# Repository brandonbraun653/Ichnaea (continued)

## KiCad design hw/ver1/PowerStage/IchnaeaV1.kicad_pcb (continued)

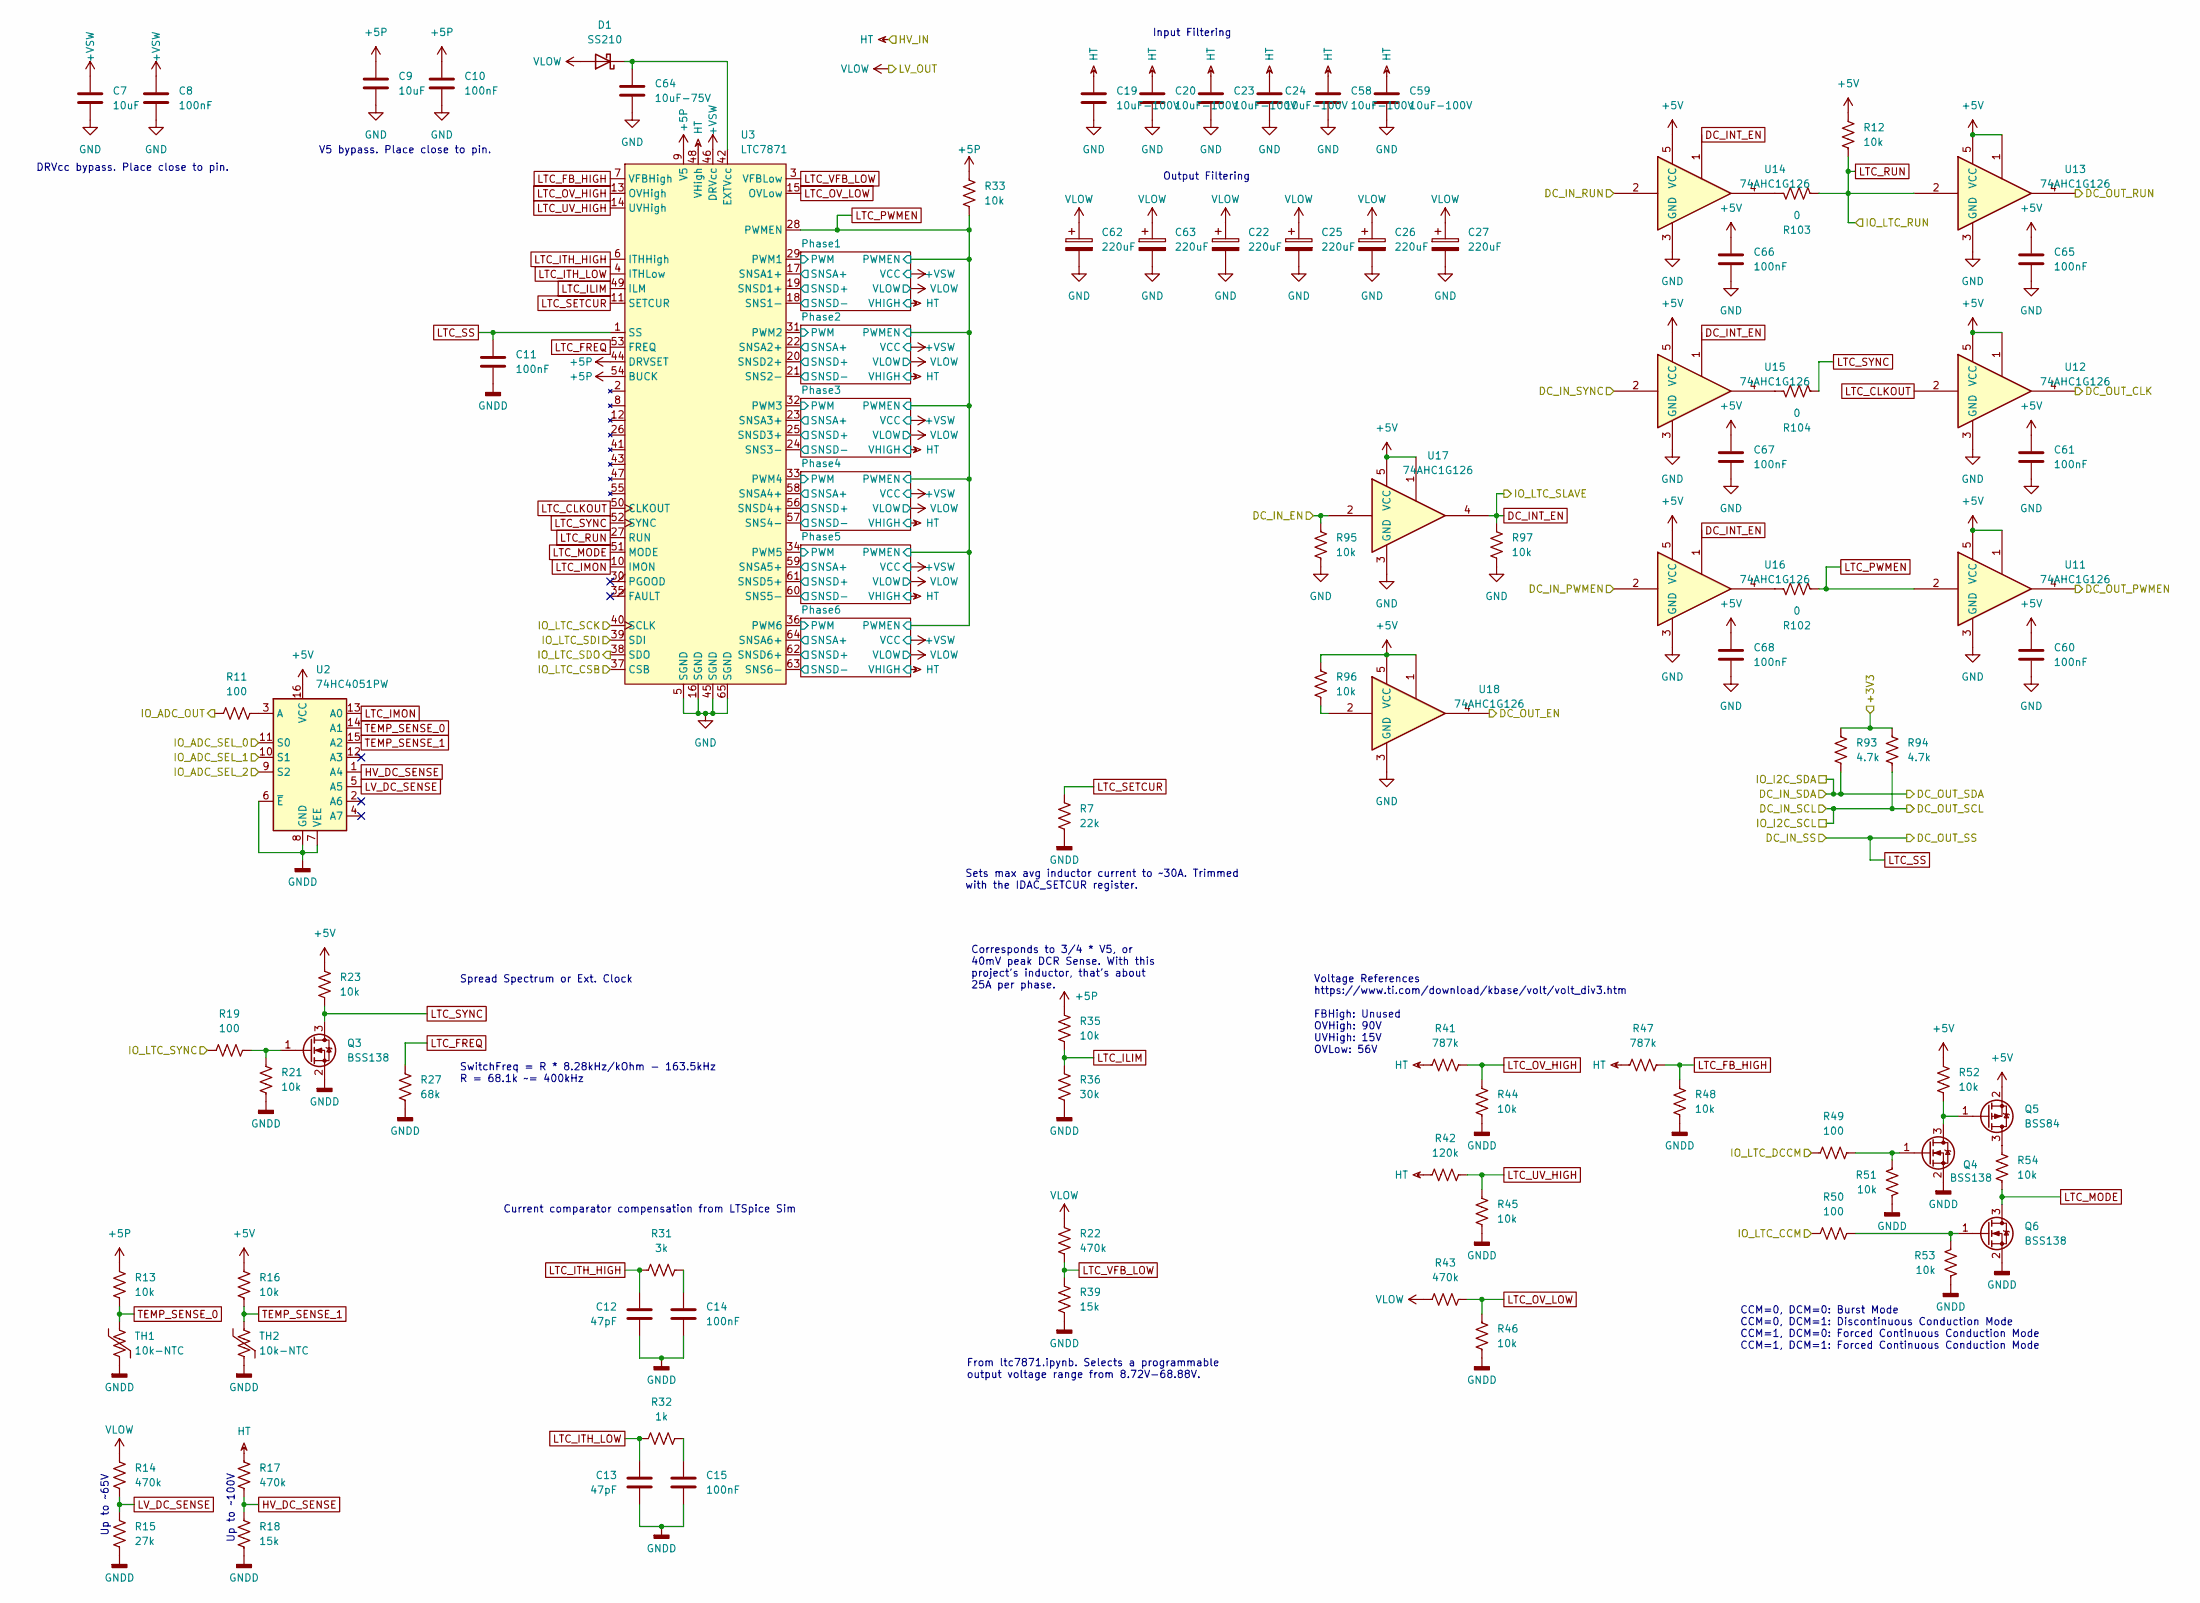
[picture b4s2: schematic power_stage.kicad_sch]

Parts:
C7, C9: 10uF; C_0603_1608Metric; Digikey N/A
C8, C10, C11, C14, C15, C60, C61, C65, C66, C67, C68: 100nF; C_0603_1608Metric; LCSC C14663
C12, C13: 47pF; C_0603_1608Metric; LCSC C1671
C19, C20, C23, C24, C58, C59: 10uF-100V; C_1210_3225Metric_Pad1.33x2.70mm_HandSolder; Digikey 490-16266-1-ND
C22, C25, C26, C27, C62, C63: 220uF; CP_Radial_D10.0mm_P5.00mm; Digikey 1189-3789-1-ND
C64: 10uF-75V; C_1210_3225Metric_Pad1.33x2.70mm_HandSolder; Digikey 445-CGA6P1X7R1N106M250ACCT-ND
D1: SS210; D_SMA; LCSC C14996
Q3, Q4, Q6: BSS138; SOT-23; Digikey 5272-BSS138CT-ND
Q5: BSS84; SOT-23; Digikey 5272-BSS84CT-ND
R7: 22k; R_0603_1608Metric; LCSC C31850
R11, R19, R49, R50: 100; R_0603_1608Metric; Digikey N/A
R12, R13, R16, R21, R23, R33, R35, R44, R45, R46, R48, R51, R52, R53, R54, R95, R96, R97: 10k; R_0603_1608Metric; LCSC C25804
R14: 470k; R_0603_1608Metric; Digikey N/A
R15: 27k; R_0603_1608Metric; Digikey N/A
R17, R22, R43: 470k; R_0603_1608Metric; LCSC C23178
R18: 15k; R_0603_1608Metric; Digikey N/A
R27: 68k; R_0603_1608Metric; Digikey N/A
R31: 3k; R_0603_1608Metric; Digikey N/A
R32: 1k; R_0603_1608Metric; Digikey N/A
R36: 30k; R_0603_1608Metric; Digikey N/A
R39: 15k; R_0603_1608Metric; LCSC C22809
R41, R47: 787k; R_0603_1608Metric_Pad0.98x0.95mm_HandSolder; Digikey P787KHCT-ND
R42: 120k; R_0603_1608Metric; Digikey N/A
R93, R94: 4.7k; R_0603_1608Metric; LCSC C23162
R102, R103, R104: 0; R_0603_1608Metric; Digikey N/A
TH1, TH2: 10k-NTC; R_0402_1005Metric_Pad0.72x0.64mm_HandSolder; Digikey 445-2550-1-ND
U2: 74HC4051PW; TSSOP-16_4.4x5mm_P0.65mm; Digikey 1727-3064-1-ND
U3: LTC7871; LQFP-64-1EP_10x10mm_P0.5mm_EP6.5x6.5mm; Digikey 505-LTC7871ELWE#PBF-ND
U11, U12, U13, U14, U15, U16, U17, U18: 74AHC1G126; SOT-353_SC-70-5_Handsoldering; Digikey 74AHCT1G126SE-7DICT-ND

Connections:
+3.3V: R93.2, R94.2; also elsewhere on the board
+5P: C9.1, C10.1, R13.2, R33.2, R35.2, U3.9 (V5), U3.44 (DRVSET), U3.54 (BUCK)
+5V: C60.1, C61.1, C65.1, C66.1, C67.1, C68.1, Q5.2 (S), R12.2, R16.2, R23.2, R52.2, R96.2, U2.16 (VCC), U11.1, U11.5 (VCC), U12.1, U12.5 (VCC), U13.1, U13.5 (VCC), U14.5 (VCC), U15.5 (VCC), U16.5 (VCC), U17.1, U17.5 (VCC), U18.1, U18.5 (VCC); also elsewhere on the board
+VSW: C7.1, C8.1, U3.46 (DRVcc); also elsewhere on the board
/ControlStage/CTL_IN_ADC: R11.1; also elsewhere on the board
/ControlStage/CTL_IN_SDI: U3.38 (SDO); also elsewhere on the board
/ControlStage/CTL_IO_SDA: R93.1; also elsewhere on the board
/ControlStage/CTL_OUT_ADC_SEL_0: U2.11 (S0); also elsewhere on the board
/ControlStage/CTL_OUT_ADC_SEL_1: U2.10 (S1); also elsewhere on the board
/ControlStage/CTL_OUT_ADC_SEL_2: U2.9 (S2); also elsewhere on the board
/ControlStage/CTL_OUT_CCM: R50.2; also elsewhere on the board
/ControlStage/CTL_OUT_DCM: R49.2; also elsewhere on the board
/ControlStage/CTL_OUT_SCL: R94.1; also elsewhere on the board
/ControlStage/CTL_OUT_SDO: U3.39 (SDI); also elsewhere on the board
/ControlStage/CTL_OUT_SYNC: R19.2; also elsewhere on the board
/ControlStage/SPI1_CSn: U3.37 (CSB); also elsewhere on the board
/ControlStage/SPI1_SCK: U3.40 (SCLK); also elsewhere on the board
/PowerStage/DC_IN_EN: R95.2, U17.2; also elsewhere on the board
/PowerStage/DC_IN_PWMEN: U16.2; also elsewhere on the board
/PowerStage/DC_IN_RUN: U14.2; also elsewhere on the board
/PowerStage/DC_IN_SYNC: U15.2; also elsewhere on the board
/PowerStage/DC_OUT_CLK: U12.4; also elsewhere on the board
/PowerStage/DC_OUT_EN: U18.4; also elsewhere on the board
/PowerStage/DC_OUT_PWMEN: U11.4; also elsewhere on the board
/PowerStage/DC_OUT_RUN: U13.4; also elsewhere on the board
/PowerStage/Phase1/PWM: U3.29 (PWM1); also elsewhere on the board
/PowerStage/Phase1/SNSA+: U3.17 (SNSA1+); also elsewhere on the board
/PowerStage/Phase1/SNSD+: U3.19 (SNSD1+); also elsewhere on the board
/PowerStage/Phase2/PWM: U3.31 (PWM2); also elsewhere on the board
/PowerStage/Phase2/SNSA+: U3.22 (SNSA2+); also elsewhere on the board
/PowerStage/Phase2/SNSD+: U3.20 (SNSD2+); also elsewhere on the board
/PowerStage/Phase3/PWM: U3.32 (PWM3); also elsewhere on the board
/PowerStage/Phase3/SNSA+: U3.23 (SNSA3+); also elsewhere on the board
/PowerStage/Phase3/SNSD+: U3.25 (SNSD3+); also elsewhere on the board
/PowerStage/Phase4/PWM: U3.33 (PWM4); also elsewhere on the board
/PowerStage/Phase4/SNSA+: U3.58 (SNSA4+); also elsewhere on the board
/PowerStage/Phase4/SNSD+: U3.56 (SNSD4+); also elsewhere on the board
/PowerStage/Phase5/PWM: U3.34 (PWM5); also elsewhere on the board
/PowerStage/Phase5/SNSA+: U3.59 (SNSA5+); also elsewhere on the board
/PowerStage/Phase5/SNSD+: U3.61 (SNSD5+); also elsewhere on the board
/PowerStage/Phase6/PWM: U3.36 (PWM6); also elsewhere on the board
/PowerStage/Phase6/SNSA+: U3.64 (SNSA6+); also elsewhere on the board
/PowerStage/Phase6/SNSD+: U3.62 (SNSD6+); also elsewhere on the board
DC_INT_EN: R97.2, U14.1, U15.1, U16.1, U17.4; also elsewhere on the board
GND: C7.2, C8.2, C9.2, C10.2, C11.2, C12.2, C13.2, C14.2, C15.2, C19.2, C20.2, C22.2, C23.2, C24.2, C25.2, C26.2, C27.2, C58.2, C59.2, C60.2, C61.2, C62.2, C63.2, C64.2, C65.2, C66.2, C67.2, C68.2, Q3.2 (S), Q4.2 (S), Q6.2 (S), R7.1, R15.1, R18.1, R21.1, R27.1, R36.1, R39.1, R44.1, R45.1, R46.1, R48.1, R51.1, R53.1, R95.1, R97.1, TH1.2, TH2.2, U2.6 (~E), U2.7 (VEE), U2.8 (GND), U3.5 (SGND), U3.16 (SGND), U3.45 (SGND), U3.65 (SGND), U11.3 (GND), U12.3 (GND), U13.3 (GND), U14.3 (GND), U15.3 (GND), U16.3 (GND), U17.3 (GND), U18.3 (GND); also elsewhere on the board
HT: C19.1, C20.1, C23.1, C24.1, C58.1, C59.1, R17.2, R41.1, R42.1, R47.1, U3.48 (VHigh); also elsewhere on the board
HV_DC_SENSE: R17.1, R18.2, U2.1 (A4)
LTC_CLKOUT: U3.50 (CLKOUT), U12.2
LTC_FB_HIGH: R47.2, R48.2, U3.7 (VFBHigh)
LTC_FREQ: R27.2, U3.53 (FREQ)
LTC_ILIM: R35.1, R36.2, U3.49 (ILM)
LTC_IMON: U2.13 (A0), U3.10 (IMON)
LTC_ITH_HIGH: C12.1, R31.2, U3.6 (ITHHigh)
LTC_ITH_LOW: C13.1, R32.2, U3.4 (ITHLow)
LTC_MODE: Q6.3 (D), R54.2, U3.51 (MODE)
LTC_OV_HIGH: R41.2, R44.2, U3.13 (OVHigh)
LTC_OV_LOW: R43.2, R46.2, U3.15 (OVLow)
LTC_PWMEN: R33.1, R102.1, U3.28 (PWMEN), U11.2; also elsewhere on the board
LTC_RUN: R12.1, R103.1, U3.27 (RUN), U13.2; also elsewhere on the board
LTC_SETCUR: R7.2, U3.11 (SETCUR)
LTC_SS: C11.1, U3.1 (SS); also elsewhere on the board
LTC_SYNC: Q3.3 (D), R23.1, R104.1, U3.52 (SYNC)
LTC_UV_HIGH: R42.2, R45.2, U3.14 (UVHigh)
LTC_VFB_LOW: R22.1, R39.2, U3.3 (VFBLow)
LV_DC_SENSE: R14.1, R15.2, U2.5 (A5)
unnamed: C14.1, R31.1
unnamed: C15.1, R32.1
unnamed: C64.1, D1.1 (K), U3.42 (EXTVcc)
unnamed: Q3.1 (G), R19.1, R21.2
unnamed: Q4.3 (D), Q5.1 (G), R52.1
unnamed: Q4.1 (G), R49.1, R51.2
unnamed: Q5.3 (D), R54.1
unnamed: Q6.1 (G), R50.1, R53.2
unnamed: R96.1, U18.2
unnamed: R102.2, U16.4
unnamed: R103.2, U14.4
unnamed: R104.2, U15.4
unnamed: R11.2, U2.3 (A)
TEMP_SENSE_0: R13.1, TH1.1, U2.14 (A1)
TEMP_SENSE_1: R16.1, TH2.1, U2.15 (A2)
VLOW: C22.1, C25.1, C26.1, C27.1, C62.1, C63.1, D1.2 (A), R14.2, R22.2, R43.1, U3.18 (SNS1-), U3.21 (SNS2-), U3.24 (SNS3-), U3.57 (SNS4-), U3.60 (SNS5-), U3.63 (SNS6-); also elsewhere on the board

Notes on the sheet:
Sets max avg inductor current to ~30A. Trimmed with the IDAC_SETCUR register.
Output Filtering
Spread Spectrum or Ext. Clock
Voltage References https://www.ti.com/download/kbase/volt/volt_div3.htm FBHigh: Unused OVHigh: 90V UVHigh: 15V OVLow: 56V
Current comparator compensation from LTSpice Sim
SwitchFreq = R * 8.28kHz/kOhm - 163.5kHz R = 68.1k ~= 400kHz
DRVcc bypass. Place close to pin.
V5 bypass. Place close to pin.
From ltc7871.ipynb. Selects a programmable output voltage range from 8.72V-68.88V.
Input Filtering
CCM=0, DCM=0: Burst Mode CCM=0, DCM=1: Discontinuous Conduction Mode CCM=1, DCM=0: Forced Continuous Conduction Mode CCM=1, DCM=1: Forced Continuous Conduction Mode
Up to ~65V
Up to ~100V
Corresponds to 3/4 * V5, or 40mV peak DCR Sense. With this project's inductor, that's about 25A per phase.

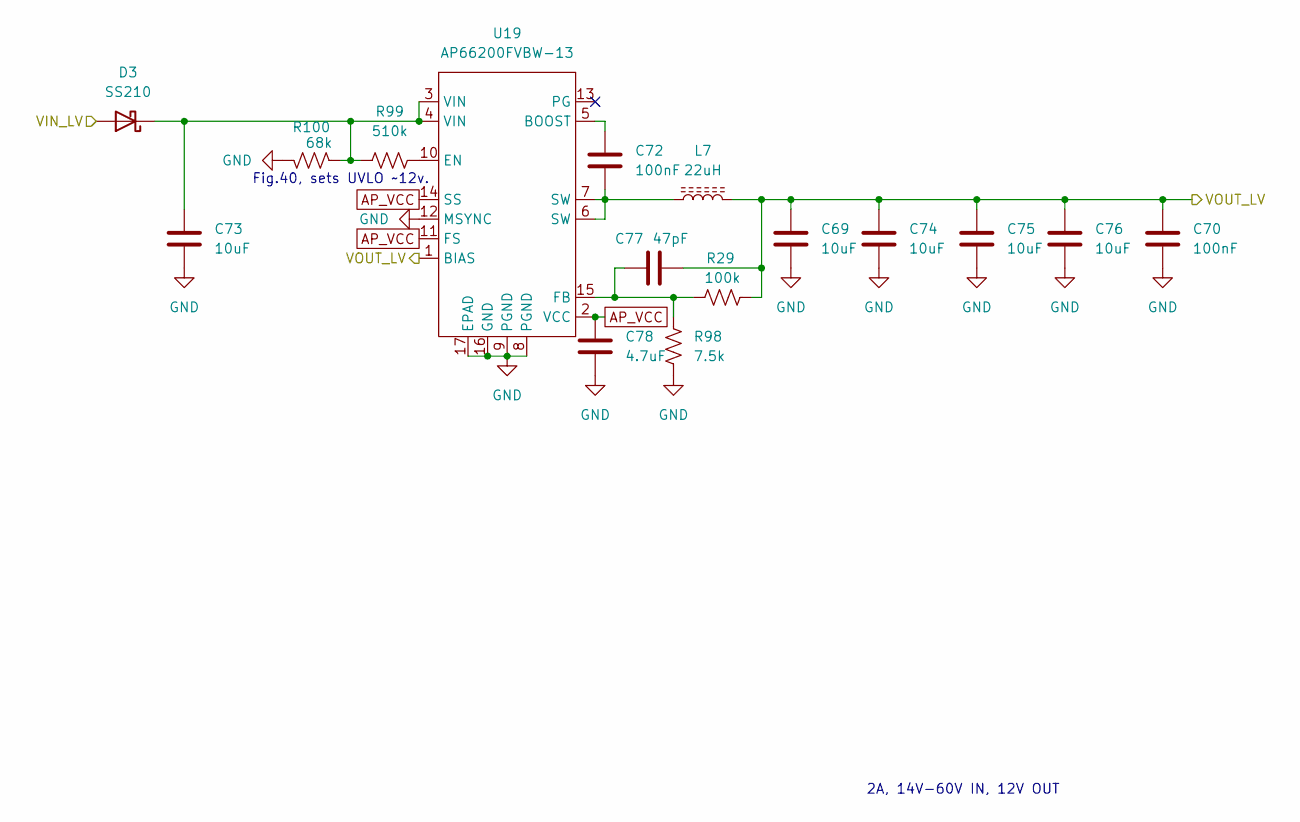
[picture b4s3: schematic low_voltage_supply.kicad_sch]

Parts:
C69, C73, C74, C75, C76: 10uF; C_0603_1608Metric; Digikey N/A
C70, C72: 100nF; C_0603_1608Metric; LCSC C14663
C77: 47pF; C_0603_1608Metric; LCSC C1671
C78: 4.7uF; C_0603_1608Metric; Digikey N/A
D3: SS210; D_SMA; LCSC C14996
L7: 22uH; TYS5020220M; Digikey 240-2706-1-ND
R29: 100k; R_0603_1608Metric; LCSC C25803
R98: 7.5k; R_0603_1608Metric; LCSC C23234
R99: 510k; R_0603_1608Metric; LCSC C23192
R100: 68k; R_0603_1608Metric; LCSC C23231
U19: AP66200FVBW-13; QFN-16-1EP_4x4mm_P0.65mm_EP2.5x2.5mm; Digikey 31-AP66200FVBW-13CT-ND

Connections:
+12V: C69.1, C70.1, C74.1, C75.1, C76.1, C77.2, L7.2, R29.2, U19.1 (BIAS); also elsewhere on the board
AP_VCC: C78.1, U19.2 (VCC), U19.11 (FS), U19.14 (SS)
GND: C69.2, C70.2, C73.2, C74.2, C75.2, C76.2, C78.2, R98.2, R100.2, U19.8 (PGND), U19.9 (PGND), U19.12 (MSYNC), U19.16 (GND), U19.17 (EPAD); also elsewhere on the board
unnamed: C72.2, L7.1, U19.6 (SW), U19.7 (SW)
unnamed: C73.1, D3.1 (K), R99.1, R100.1, U19.3 (VIN), U19.4 (VIN)
unnamed: C72.1, U19.5 (BOOST)
unnamed: R99.2, U19.10 (EN)
unnamed: C77.1, R29.1, R98.1, U19.15 (FB)
VLOW: D3.2 (A); also elsewhere on the board

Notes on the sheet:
2A, 14V-60V IN, 12V OUT
Fig.40, sets UVLO ~12v.

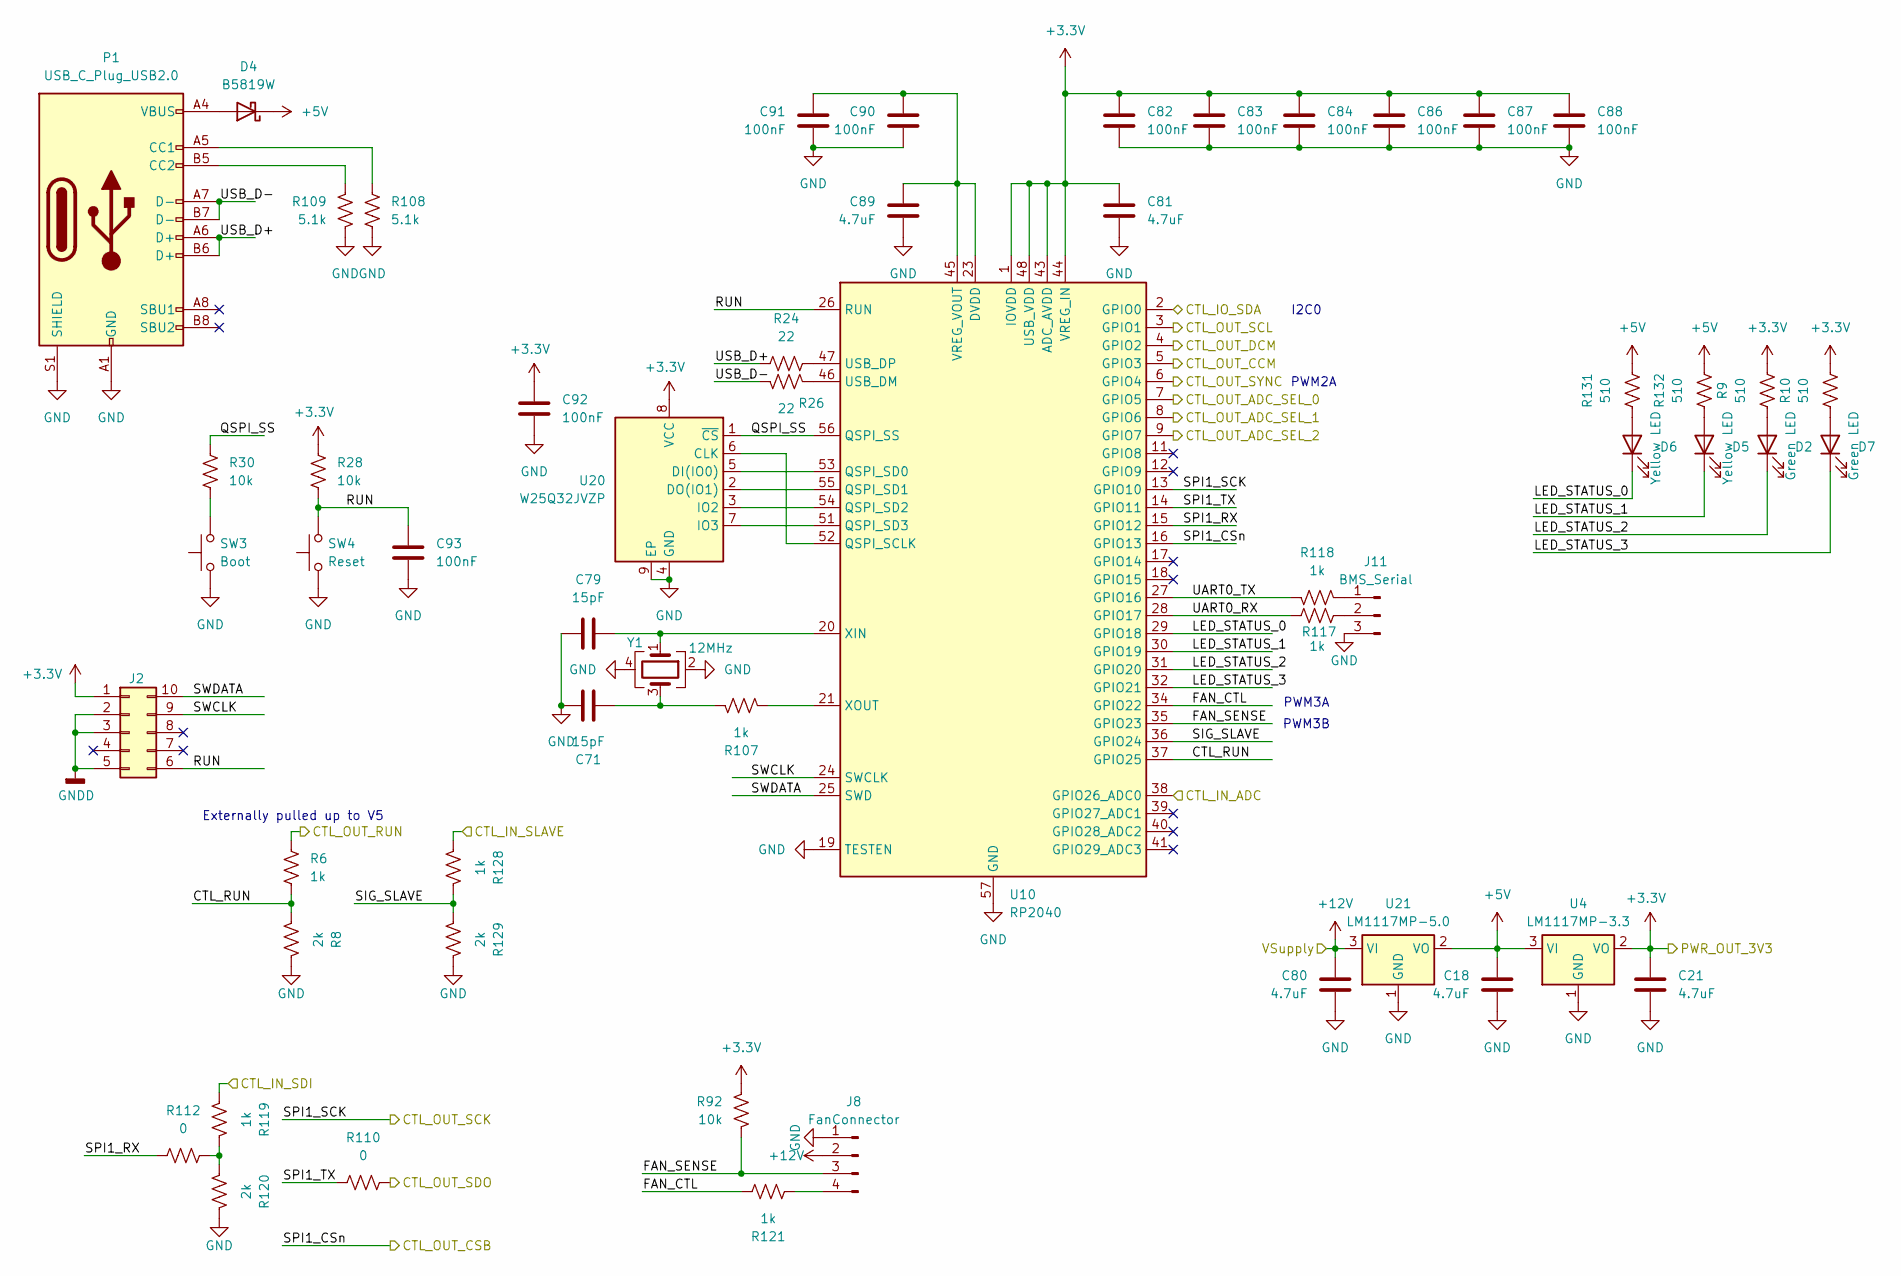
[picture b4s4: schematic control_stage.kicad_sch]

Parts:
C18, C21, C80, C81, C89: 4.7uF; C_0603_1608Metric; Digikey N/A
C71, C79: 15pF; C_0603_1608Metric; Digikey N/A
C82, C83, C84, C86, C87, C88, C90, C91, C92, C93: 100nF; C_0603_1608Metric; LCSC C14663
D2, D7: Green LED; LED_0805_2012Metric; LCSC C2297
D4: B5819W; D_SOD-123; LCSC C8598
D5, D6: Yellow LED; LED_0805_2012Metric; LCSC C2296
J2: JTAG_2x05_P1_27mm_Shrouded_SMD; Digikey 1175-1629-ND
J8: FanConnector; Molex_KK-254_AE-6410-04A_1x04_P2.54mm_Vertical; Digikey WM4330-ND
J11: BMS_Serial; Harwin_M20-89003xx_1x03_P2.54mm_Horizontal; Digikey 952-3232-ND
P1: USB_C_Plug_USB2.0; USB_C_Receptacle_GCT_USB4085; Digikey 2073-USB4085-GF-ACT-ND
R6, R107, R117, R118, R119, R121, R128: 1k; R_0603_1608Metric; Digikey N/A
R8, R120, R129: 2k; R_0603_1608Metric; Digikey N/A
R9, R10, R131, R132: 510; R_0603_1608Metric; Digikey N/A
R24, R26: 22; R_0603_1608Metric; LCSC C23345
R28, R30, R92: 10k; R_0603_1608Metric; LCSC C25804
R108, R109: 5.1k; R_0603_1608Metric; LCSC C23186
R110, R112: 0; R_0603_1608Metric; Digikey N/A
SW3: Boot; SW_SPST_EVQP2; Digikey P11081SCT-ND
SW4: Reset; SW_SPST_EVQP2; Digikey P11081SCT-ND
U4: LM1117MP-3.3; SOT-223-3_TabPin2; Digikey N/A
U10: RP2040; QFN-56-1EP_7x7mm_P0.4mm_EP3.2x3.2mm; Digikey 2648-SC0914(13)CT-ND
U20: W25Q32JVZP; WSON-8-1EP_6x5mm_P1.27mm_EP3.4x4.3mm; Digikey W25Q32JVZPIQ-ND
U21: LM1117MP-5.0; SOT-223-3_TabPin2; LCSC C6187
Y1: 12MHz; Crystal_SMD_3225-4Pin_3.2x2.5mm; Digikey XC2613CT-ND

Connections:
+3.3V: C21.1, C81.1, C82.1, C83.1, C84.1, C86.1, C87.1, C88.1, C92.1, J2.1, R9.1, R10.1, R28.2, R92.2, U4.2 (VO), U10.1 (IOVDD), U10.10 (IOVDD), U10.22 (IOVDD), U10.33 (IOVDD), U10.42 (IOVDD), U10.43 (ADC_AVDD), U10.44 (VREG_IN), U10.48 (USB_VDD), U10.49 (IOVDD), U20.8 (VCC); also elsewhere on the board
+5V: C18.1, D4.1 (K), R131.1, R132.1, U4.3 (VI), U21.2 (VO); also elsewhere on the board
+12V: C80.1, J8.2, U21.3 (VI); also elsewhere on the board
/ControlStage/CTL_IN_ADC: U10.38 (GPIO26_ADC0); also elsewhere on the board
/ControlStage/CTL_IN_SDI: R119.2; also elsewhere on the board
/ControlStage/CTL_IO_SDA: U10.2 (GPIO0); also elsewhere on the board
/ControlStage/CTL_OUT_ADC_SEL_0: U10.7 (GPIO5); also elsewhere on the board
/ControlStage/CTL_OUT_ADC_SEL_1: U10.8 (GPIO6); also elsewhere on the board
/ControlStage/CTL_OUT_ADC_SEL_2: U10.9 (GPIO7); also elsewhere on the board
/ControlStage/CTL_OUT_CCM: U10.5 (GPIO3); also elsewhere on the board
/ControlStage/CTL_OUT_DCM: U10.4 (GPIO2); also elsewhere on the board
/ControlStage/CTL_OUT_SCL: U10.3 (GPIO1); also elsewhere on the board
/ControlStage/CTL_OUT_SDO: R110.1; also elsewhere on the board
/ControlStage/CTL_OUT_SYNC: U10.6 (GPIO4); also elsewhere on the board
/ControlStage/CTL_RUN: R6.1, R8.2, U10.37 (GPIO25)
/ControlStage/FAN_CTL: R121.2, U10.34 (GPIO22)
/ControlStage/FAN_SENSE: J8.3, R92.1, U10.35 (GPIO23)
/ControlStage/LED_STATUS_0: D6.1 (K), U10.29 (GPIO18)
/ControlStage/LED_STATUS_1: D5.1 (K), U10.30 (GPIO19)
/ControlStage/LED_STATUS_2: D2.1 (K), U10.31 (GPIO20)
/ControlStage/LED_STATUS_3: D7.1 (K), U10.32 (GPIO21)
/ControlStage/QSPI_SS: R30.2, U10.56 (QSPI_SS), U20.1 (~CS)
/ControlStage/RUN: C93.1, J2.6, R28.1, SW4.2, U10.26 (RUN)
/ControlStage/SIG_SLAVE: R128.1, R129.2, U10.36 (GPIO24)
/ControlStage/SPI1_CSn: U10.16 (GPIO13); also elsewhere on the board
/ControlStage/SPI1_RX: R112.2, U10.15 (GPIO12)
/ControlStage/SPI1_SCK: U10.13 (GPIO10); also elsewhere on the board
/ControlStage/SPI1_TX: R110.2, U10.14 (GPIO11)
/ControlStage/SWCLK: J2.9, U10.24 (SWCLK)
/ControlStage/SWDATA: J2.10, U10.25 (SWD)
/ControlStage/UART0_RX: R117.2, U10.28 (GPIO17)
/ControlStage/UART0_TX: R118.2, U10.27 (GPIO16)
/ControlStage/USB_D+: P1.A6 (D+), P1.B6 (D+), R24.2
/ControlStage/USB_D-: P1.A7 (D-), P1.B7 (D-), R26.2
DC_INT_EN: R128.2; also elsewhere on the board
GND: C18.2, C21.2, C71.1, C79.1, C80.2, C81.2, C82.2, C83.2, C84.2, C86.2, C87.2, C88.2, C89.2, C90.2, C91.2, C92.2, C93.2, J2.2, J2.3, J2.5, J8.1, J11.3, P1.A1 (GND), P1.A12 (GND), P1.B1 (GND), P1.B12 (GND), P1.S1 (SHIELD), R8.1, R108.1, R109.1, R120.1, R129.1, SW3.1, SW4.1, U4.1 (GND), U10.19 (TESTEN), U10.57 (GND), U20.4 (GND), U20.9 (EP), U21.1 (GND), Y1.2, Y1.4; also elsewhere on the board
LTC_RUN: R6.2; also elsewhere on the board
unnamed: C71.2, R107.1, Y1.3
unnamed: D2.2 (A), R9.2
unnamed: D4.2 (A), P1.A4 (VBUS), P1.A9 (VBUS), P1.B4 (VBUS), P1.B9 (VBUS)
unnamed: D5.2 (A), R132.2
unnamed: D6.2 (A), R131.2
unnamed: D7.2 (A), R10.2
unnamed: J8.4, R121.1
unnamed: J11.1, R118.1
unnamed: J11.2, R117.1
unnamed: P1.A5 (CC1), R108.2
unnamed: P1.B5 (CC2), R109.2
unnamed: R30.1, SW3.2
unnamed: R112.1, R119.1, R120.2
unnamed: U10.52 (QSPI_SCLK), U20.6 (CLK)
unnamed: U10.53 (QSPI_SD0), U20.5 (DI(IO0))
unnamed: U10.55 (QSPI_SD1), U20.2 (DO(IO1))
unnamed: U10.54 (QSPI_SD2), U20.3 (IO2)
unnamed: U10.51 (QSPI_SD3), U20.7 (IO3)
unnamed: R26.1, U10.46 (USB_DM)
unnamed: R24.1, U10.47 (USB_DP)
unnamed: C89.1, C90.1, C91.1, U10.23 (DVDD), U10.45 (VREG_VOUT), U10.50 (DVDD)
unnamed: C79.2, U10.20 (XIN), Y1.1
unnamed: R107.2, U10.21 (XOUT)

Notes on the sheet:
PWM3A
PWM2A
I2C0
PWM3B
Externally pulled up to V5

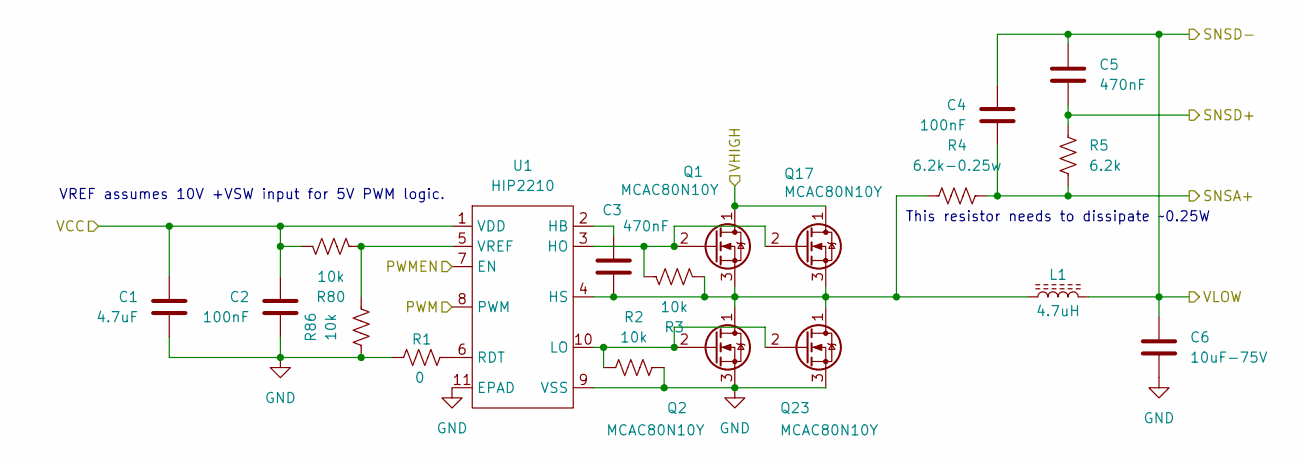
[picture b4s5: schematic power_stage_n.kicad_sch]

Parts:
C1: 4.7uF; C_0603_1608Metric; Digikey N/A
C2, C4: 100nF; C_0603_1608Metric; LCSC C14663
C3, C5: 470nF; C_0603_1608Metric; Digikey N/A
C6: 10uF-75V; C_1210_3225Metric_Pad1.33x2.70mm_HandSolder; Digikey 445-CGA6P1X7R1N106M250ACCT-ND
L1: 4.7uH; Bournes_L_PQ2614BLA; Digikey PQ2614BLA-3R3K-ND
Q1, Q2, Q17, Q23: MCAC80N10Y; TRANS_BSC076N06NS3-G; Digikey 353-MCAC80N10Y-TPCT-ND
R1: 0; R_0603_1608Metric; Digikey N/A
R2, R3, R80, R86: 10k; R_0603_1608Metric; LCSC C25804
R4: 6.2k-0.25w; R_1206_3216Metric_Pad1.30x1.75mm_HandSolder; Digikey 311-6.20KFRCT-ND
R5: 6.2k; R_0603_1608Metric; Digikey N/A
U1: HIP2210; TDFN-10-1EP_4x4mm_P0.8mm_EP2.6x3mm; Digikey 20-HIP2210FRTZ-TCT-ND

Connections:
+VSW: C1.1, C2.1, R80.2, U1.1 (VDD); also elsewhere on the board
/PowerStage/Phase1/PWM: U1.8 (PWM); also elsewhere on the board
/PowerStage/Phase1/SNSA+: C4.2, R4.2, R5.2; also elsewhere on the board
/PowerStage/Phase1/SNSD+: C5.2, R5.1; also elsewhere on the board
GND: C1.2, C2.2, C6.2, Q2.3 (S), Q23.3 (S), R1.1, R2.1, R86.2, U1.9 (VSS), U1.11 (EPAD); also elsewhere on the board
HT: Q1.1 (D), Q17.1 (D); also elsewhere on the board
LTC_PWMEN: U1.7 (EN); also elsewhere on the board
unnamed: Q1.2 (G), Q17.2 (G), R3.2, U1.3 (HO)
unnamed: C3.2, L1.1, Q1.3 (S), Q2.1 (D), Q17.3 (S), Q23.1 (D), R3.1, R4.1, U1.4 (HS)
unnamed: Q2.2 (G), Q23.2 (G), R2.2, U1.10 (LO)
unnamed: C3.1, U1.2 (HB)
unnamed: R1.2, U1.6 (RDT)
unnamed: R80.1, R86.1, U1.5 (VREF)
VLOW: C4.1, C5.1, C6.1, L1.2; also elsewhere on the board

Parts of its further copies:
C28, C34, C40, C46, C52: 4.7uF; C_0603_1608Metric; Digikey N/A
C29, C31, C35, C37, C41, C43, C47, C49, C53, C55: 100nF; C_0603_1608Metric; LCSC C14663
C30, C32, C36, C38, C42, C44, C48, C50, C54, C56: 470nF; C_0603_1608Metric; Digikey N/A
C33, C39, C45, C51, C57: 10uF-75V; C_1210_3225Metric_Pad1.33x2.70mm_HandSolder; Digikey 445-CGA6P1X7R1N106M250ACCT-ND
L2, L3, L4, L5, L6: 4.7uH; Bournes_L_PQ2614BLA; Digikey PQ2614BLA-3R3K-ND
Q7, Q8, Q9, Q10, Q11, Q12, Q13, Q14, Q15, Q16, Q18, Q19, Q20, Q21, Q22, Q24, Q25, Q26, Q27, Q28: MCAC80N10Y; TRANS_BSC076N06NS3-G; Digikey 353-MCAC80N10Y-TPCT-ND
R55, R60, R65, R70, R75: 0; R_0603_1608Metric; Digikey N/A
R56, R57, R61, R62, R66, R67, R71, R72, R76, R77, R81, R82, R83, R84, R85, R87, R88, R89, R90, R91: 10k; R_0603_1608Metric; LCSC C25804
R58, R63, R68, R73, R78: 6.2k-0.25w; R_1206_3216Metric_Pad1.30x1.75mm_HandSolder; Digikey 311-6.20KFRCT-ND
R59, R64, R69, R74, R79: 6.2k; R_0603_1608Metric; Digikey N/A
U5, U6, U7, U8, U9: HIP2210; TDFN-10-1EP_4x4mm_P0.8mm_EP2.6x3mm; Digikey 20-HIP2210FRTZ-TCT-ND

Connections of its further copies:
+VSW: C28.1, C29.1, C34.1, C35.1, C40.1, C41.1, C46.1, C47.1, C52.1, C53.1, R81.2, R82.2, R83.2, R84.2, R85.2, U5.1 (VDD), U6.1 (VDD), U7.1 (VDD), U8.1 (VDD), U9.1 (VDD); also elsewhere on the board
/PowerStage/Phase2/PWM: U5.8 (PWM); also elsewhere on the board
/PowerStage/Phase2/SNSA+: C31.2, R58.2, R59.2; also elsewhere on the board
/PowerStage/Phase2/SNSD+: C32.2, R59.1; also elsewhere on the board
/PowerStage/Phase3/PWM: U6.8 (PWM); also elsewhere on the board
/PowerStage/Phase3/SNSA+: C37.2, R63.2, R64.2; also elsewhere on the board
/PowerStage/Phase3/SNSD+: C38.2, R64.1; also elsewhere on the board
/PowerStage/Phase4/PWM: U7.8 (PWM); also elsewhere on the board
/PowerStage/Phase4/SNSA+: C43.2, R68.2, R69.2; also elsewhere on the board
/PowerStage/Phase4/SNSD+: C44.2, R69.1; also elsewhere on the board
/PowerStage/Phase5/PWM: U8.8 (PWM); also elsewhere on the board
/PowerStage/Phase5/SNSA+: C49.2, R73.2, R74.2; also elsewhere on the board
/PowerStage/Phase5/SNSD+: C50.2, R74.1; also elsewhere on the board
/PowerStage/Phase6/PWM: U9.8 (PWM); also elsewhere on the board
/PowerStage/Phase6/SNSA+: C55.2, R78.2, R79.2; also elsewhere on the board
/PowerStage/Phase6/SNSD+: C56.2, R79.1; also elsewhere on the board
GND: C28.2, C29.2, C33.2, C34.2, C35.2, C39.2, C40.2, C41.2, C45.2, C46.2, C47.2, C51.2, C52.2, C53.2, C57.2, Q8.3 (S), Q10.3 (S), Q12.3 (S), Q14.3 (S), Q16.3 (S), Q24.3 (S), Q25.3 (S), Q26.3 (S), Q27.3 (S), Q28.3 (S), R55.1, R56.1, R60.1, R61.1, R65.1, R66.1, R70.1, R71.1, R75.1, R76.1, R87.2, R88.2, R89.2, R90.2, R91.2, U5.9 (VSS), U5.11 (EPAD), U6.9 (VSS), U6.11 (EPAD), U7.9 (VSS), U7.11 (EPAD), U8.9 (VSS), U8.11 (EPAD), U9.9 (VSS), U9.11 (EPAD); also elsewhere on the board
HT: Q7.1 (D), Q9.1 (D), Q11.1 (D), Q13.1 (D), Q15.1 (D), Q18.1 (D), Q19.1 (D), Q20.1 (D), Q21.1 (D), Q22.1 (D); also elsewhere on the board
LTC_PWMEN: U5.7 (EN), U6.7 (EN), U7.7 (EN), U8.7 (EN), U9.7 (EN); also elsewhere on the board
unnamed: C36.2, L3.1, Q9.3 (S), Q10.1 (D), Q19.3 (S), Q25.1 (D), R62.1, R63.1, U6.4 (HS)
unnamed: Q10.2 (G), Q25.2 (G), R61.2, U6.10 (LO)
unnamed: Q11.2 (G), Q20.2 (G), R67.2, U7.3 (HO)
unnamed: C42.2, L4.1, Q11.3 (S), Q12.1 (D), Q20.3 (S), Q26.1 (D), R67.1, R68.1, U7.4 (HS)
unnamed: Q12.2 (G), Q26.2 (G), R66.2, U7.10 (LO)
unnamed: Q13.2 (G), Q21.2 (G), R72.2, U8.3 (HO)
unnamed: C48.2, L5.1, Q13.3 (S), Q14.1 (D), Q21.3 (S), Q27.1 (D), R72.1, R73.1, U8.4 (HS)
unnamed: Q14.2 (G), Q27.2 (G), R71.2, U8.10 (LO)
unnamed: Q15.2 (G), Q22.2 (G), R77.2, U9.3 (HO)
unnamed: C54.2, L6.1, Q15.3 (S), Q16.1 (D), Q22.3 (S), Q28.1 (D), R77.1, R78.1, U9.4 (HS)
unnamed: Q16.2 (G), Q28.2 (G), R76.2, U9.10 (LO)
unnamed: Q7.2 (G), Q18.2 (G), R57.2, U5.3 (HO)
unnamed: C30.2, L2.1, Q7.3 (S), Q8.1 (D), Q18.3 (S), Q24.1 (D), R57.1, R58.1, U5.4 (HS)
unnamed: Q9.2 (G), Q19.2 (G), R62.2, U6.3 (HO)
unnamed: Q8.2 (G), Q24.2 (G), R56.2, U5.10 (LO)
unnamed: C30.1, U5.2 (HB)
unnamed: R55.2, U5.6 (RDT)
unnamed: R81.1, R87.1, U5.5 (VREF)
unnamed: C36.1, U6.2 (HB)
unnamed: R60.2, U6.6 (RDT)
unnamed: R82.1, R88.1, U6.5 (VREF)
unnamed: C42.1, U7.2 (HB)
unnamed: R65.2, U7.6 (RDT)
unnamed: R83.1, R89.1, U7.5 (VREF)
unnamed: C48.1, U8.2 (HB)
unnamed: R70.2, U8.6 (RDT)
unnamed: R84.1, R90.1, U8.5 (VREF)
unnamed: C54.1, U9.2 (HB)
unnamed: R75.2, U9.6 (RDT)
unnamed: R85.1, R91.1, U9.5 (VREF)
VLOW: C31.1, C32.1, C33.1, C37.1, C38.1, C39.1, C43.1, C44.1, C45.1, C49.1, C50.1, C51.1, C55.1, C56.1, C57.1, L2.2, L3.2, L4.2, L5.2, L6.2; also elsewhere on the board

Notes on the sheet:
VREF assumes 10V +VSW input for 5V PWM logic.
This resistor needs to dissipate ~0.25W
